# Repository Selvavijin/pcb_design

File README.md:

# pcb_design

The tunnels or holes are covered by copper. There is a core present in the middle and the copper layers cover the core. We focus on 2 layer board. so, we have a core and 2 copper layers.

The gray colour represents the core and the two yellow layers represent copper layers. In KiCAD, front copper layer is red in colour and back copper layer is blue in colour.

Silkscreen is used to add the important informations like adding the names or writing any text.

LUT means gates. 1 LUT means 1 gate(AND, OR, etc). This has 5K LUTs

Here we are going to learn about making production ready shields for specific applications for our projects.

KiCAD is the open source tool and the other two are commertial tools. But the workflow of all the three are similar.

This is the application that we are going to focus on. We need to use this with an FPGA and create a shield for it. Let us see how

Creating a new project in KICad will create two files. One is .kicad_sch file and the other is .kicad_pcb.

Initially we will look into the schmatic file

We can goto the 'place' option at the top or click 'a' to open the symbol library which has the collection of symbols.

The below shown is the very simple design. 'w' is used for wiring purpose.

Now, let us move to the actual design.
We can goto 'https://github.com/yathAg/VSDSquadron_FM_Workshop' and download the required libraries. Then we have to necessoryly save the library in the same folder as our project. We have 3 folders inside the library file. Symbole - it has a .bak(back up) file and a symbol file. To add this in kicad, goto preferences->manage symbol libraries->project specific libraries and select the file.

Then we will search for Gyroscope(ICM 4267) which is required for our project. This is also not available in the symbols. So, we go to 'snapeda' and search for 'icm 4267' and download and use it as we did for the previous symbol.

For any design, the reference manual is the datasheet of the device so, we will download it from the website 'https://invensense.tdk.com/products/motion-tracking/6-axis/icm-42670-p/'. For schmatic capture, there are two important characteristics, one is the pin description. So, fromm the datasheet, it is observed that there are two communication protocols used I3C and SPI interface. In this workshop, SPI part is focussed.

By looking into the pin configuration, we do the connections. RESV is reserved and no connection, so we press 'q' and give the cross symbol. When we connect the entire circuits with the wires, it will too crowded. So, to avoid that problem, we are using labels eg: AP_CS.

To check whether they are connected using label we can use the highlighter. Which are the pins are highlighted while clicking in a pin, they are connected to each other.

Then we have to add Decoupling capacitors as shown in the datasheet to make sure that the circuit works correctly.

Then we have to give connectins to the 4 pin header. The main thing we have to make sure is the power requirements is met. The power supply on the VSD Squadron FM does not used to power up the shield. So, we need to use external power supply. The common thing that is used is an LDO which can be found from the website'mouser.com' and search for LDO and apply filters like '1 output' and '-3.3v' output voltage and we will have multiple options. We can search ams1117-3.3 in google and enter into the website 'digikey' and find the datasheet.

This component is commonly available and we can find it in the symbols itself. The one end is connected to the 5V of the VSD Squadron and the other end is connected to 3.3V and the third end is connected to gnd. Also we connect capacitors by referring into the data sheet.

Then we give title by double clicking in the bottom. Then we partition the circuits using a line. This is the schmetic.

Then we are going to do ERC rule check. Inspect->Electrical rule checker->run erc.

Here we can ignore the 2 errors, because we are going to connect the supply directly from VSDSquadron. However, if we need to remove those errors, we can connect the pins to the power flags as shown below.

Then we have to assign footprints. click on assign footprints. Here there is no footprints assigned for the capacitors. But the footprints are assigned for the next two devices but it can't be found and the last one has footprint in kicad itself.

So, we need to know, how to set footprints for the capacitors by going to the reference document in 'https://github.com/yathAg/VSDSquadron_FM_Workshop'. We select the below footprint for all the capacitors.

To select the footprint for the ICM kit, we need to goto the datasheet and refer. Here, pitch is the interconnect between two pins. Here it is 'e' and is set to 0.5.

From the below picture, we get that we have to search 'LGA' for the footprint, so we double click the schematic and select the required footprint.

Then we also add the footprint for the VSDSquadron from the local directory and now the footprints are assigned for everything.

As a designer, we have to make connections with minimum resistance.

In KiCAD we are making a small change for the 10 and 22um capacitor in footprint as a bigger size.

Once that is done, we can move to the PCB editor and the below window appears.

To create a new project, goto File->Board setup. The user layers are not required now, so we disabled it.

Then moving to physical stackup, we are customizing the colours of layers and also we can customize the thickness and material.

Moving to 'constraints'. If we do more designs, we can use the option 'import settings from another board'. Otherwise, manually we have to set it according to the manufacturer. Now we stick to 'JLCPCB' manufacturer. The detailed document can be found in the reference document. And the capabilities of JLCPCB can be found in 'https://jlcpcb.com/capabilities/pcb-capabilities'.

Then we can move to 'pre-defined sizes'

Now the entire setup is complete. 
Now we select the 50 mils.

The three sets of capacitors that are together are called de-coupling capacitors and should be placed as close to the power pins as shown in the schematic.

Then we organize the silkscreen. Then we draw the board boundary. So, we select the edgecuts layer and draw boundary.

Then we are going to make the copper zones. There are two layers top and bottom. On bottom, we are going to add a gnd zone.

If we see down, we can see 25 unrouted nets and if we press 'b', it fills out the copper zone as shown below.

Now, all the gnd are connected on the bottom layer and are remaining in the top layer. On the front layer, we are going to give 3.3v zone as we given for the gnd.

When we press 'b' again, all the 3.3v are connected.

But, it is missed in some places as shown below because of the minimum width and the clearance that we selected.

If we reduce the clearance value, it will affect the circuit. So we are going to give connection using wires. 

While we give connections, we face difficulty in routing as shown above. So, will change the pins in the schematic as shown below.

We can click 'v' for a via and use it.

Then we do connect gnd signals by using the via.

Then we do connect 5V signal using 20 mil trace.

In pin number 8 and 5, the connection is not done due to clearance. So we connect it with a place trace as shown below.

Once these things are done, we click 'b' again.

Then we go to the 3d viewer and get an idea on how the PCB looks like.

There are more empty space and we can go to the silkscreen layer to add any texts. 

We can add the texts in a fancier manner by clicking on the plugin and content manager->Kibuzzard on the home screen. 

Once that is done, we can go to preferences->action plugin.

The next step is to run the DRC checker and we can exclude the error that are obtained. Because, we have checked them already.

Now let us move to generate the gerber files. For that we can either go to the 'plot' option and generate according to the fabrication house else we goto the plugins and content manager and search for 'jlcpcb'.

We have to add something called 'lcsc' for the JLCPCB so to do that we goto the schematic and go to bulk edit and add the field LCSC. So that this will be added in the bom and used by the fabrication house.

Then we do the same for 'ICM-42670-P'.

Similarly we need to do for 'AMS1117-3.3' and other capacitors.

Then we update PCB and again generate the gerber files.

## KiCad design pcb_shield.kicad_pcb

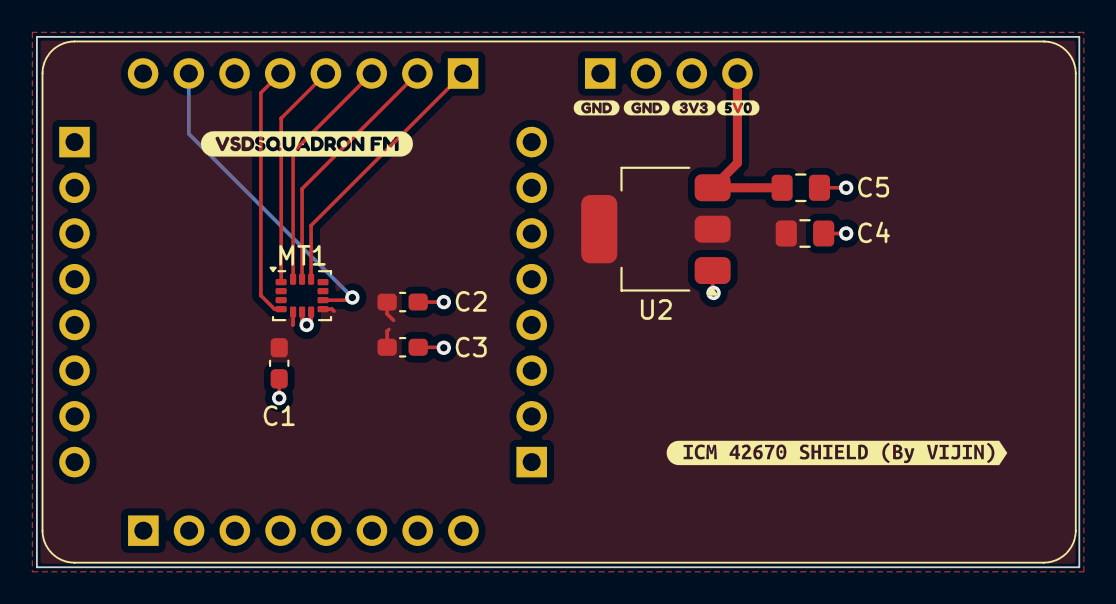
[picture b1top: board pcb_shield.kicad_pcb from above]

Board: 2 copper layers, 57.9 x 29.5 mm, 9 parts (0 on the bottom side), 9 nets.

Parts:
C1: 10nF; C_0603_1608Metric_Pad1.08x0.95mm_HandSolder
C2: 0.1uF; C_0603_1608Metric_Pad1.08x0.95mm_HandSolder
C3: 2.2uF; C_0603_1608Metric_Pad1.08x0.95mm_HandSolder
C4: 22uF; C_0805_2012Metric_Pad1.18x1.45mm_HandSolder
C5: 10uF; C_0805_2012Metric_Pad1.18x1.45mm_HandSolder
MT1: ICM-42670-P; LGA-14_3x2.5mm_P0.5mm_LayoutBorder3x4y
U1: VSDSquadron FM; VSDSquadron_FM
U2: AMS1117-3.3; SOT-223-3_TabPin2
kibuzzard-678674B4: G***; kibuzzard-678674B4

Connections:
+3.3V: C1.1, C2.1, C3.1, C4.1, MT1.5 (VDDIO), MT1.8 (VDD), U2.2 (VO)
+5V: C5.1, U1.36 (5V0), U2.3 (VI)
/AP_CS: MT1.12 (AP_CS), U1.17 (13)
/AP_SCL: MT1.13 (AP_SCL/AP_SCLK), U1.18
/AP_SDIO: MT1.14 (AP_SDA/AP_SDIO/AP_SDI), U1.19
/AP_SDO: MT1.1 (AP_SDO/AP_AD0), U1.20 (21)
/INT1: MT1.4 (INT1/INT), U1.21 (23)
/INT2: MT1.9 (INT2), U1.23 (25)
GND: C1.2, C2.2, C3.2, C4.2, C5.2, MT1.6 (GND), MT1.7 (FSYNC), U1.22 (GND), U1.33 (GND), U1.34 (GND), U2.1 (GND)
